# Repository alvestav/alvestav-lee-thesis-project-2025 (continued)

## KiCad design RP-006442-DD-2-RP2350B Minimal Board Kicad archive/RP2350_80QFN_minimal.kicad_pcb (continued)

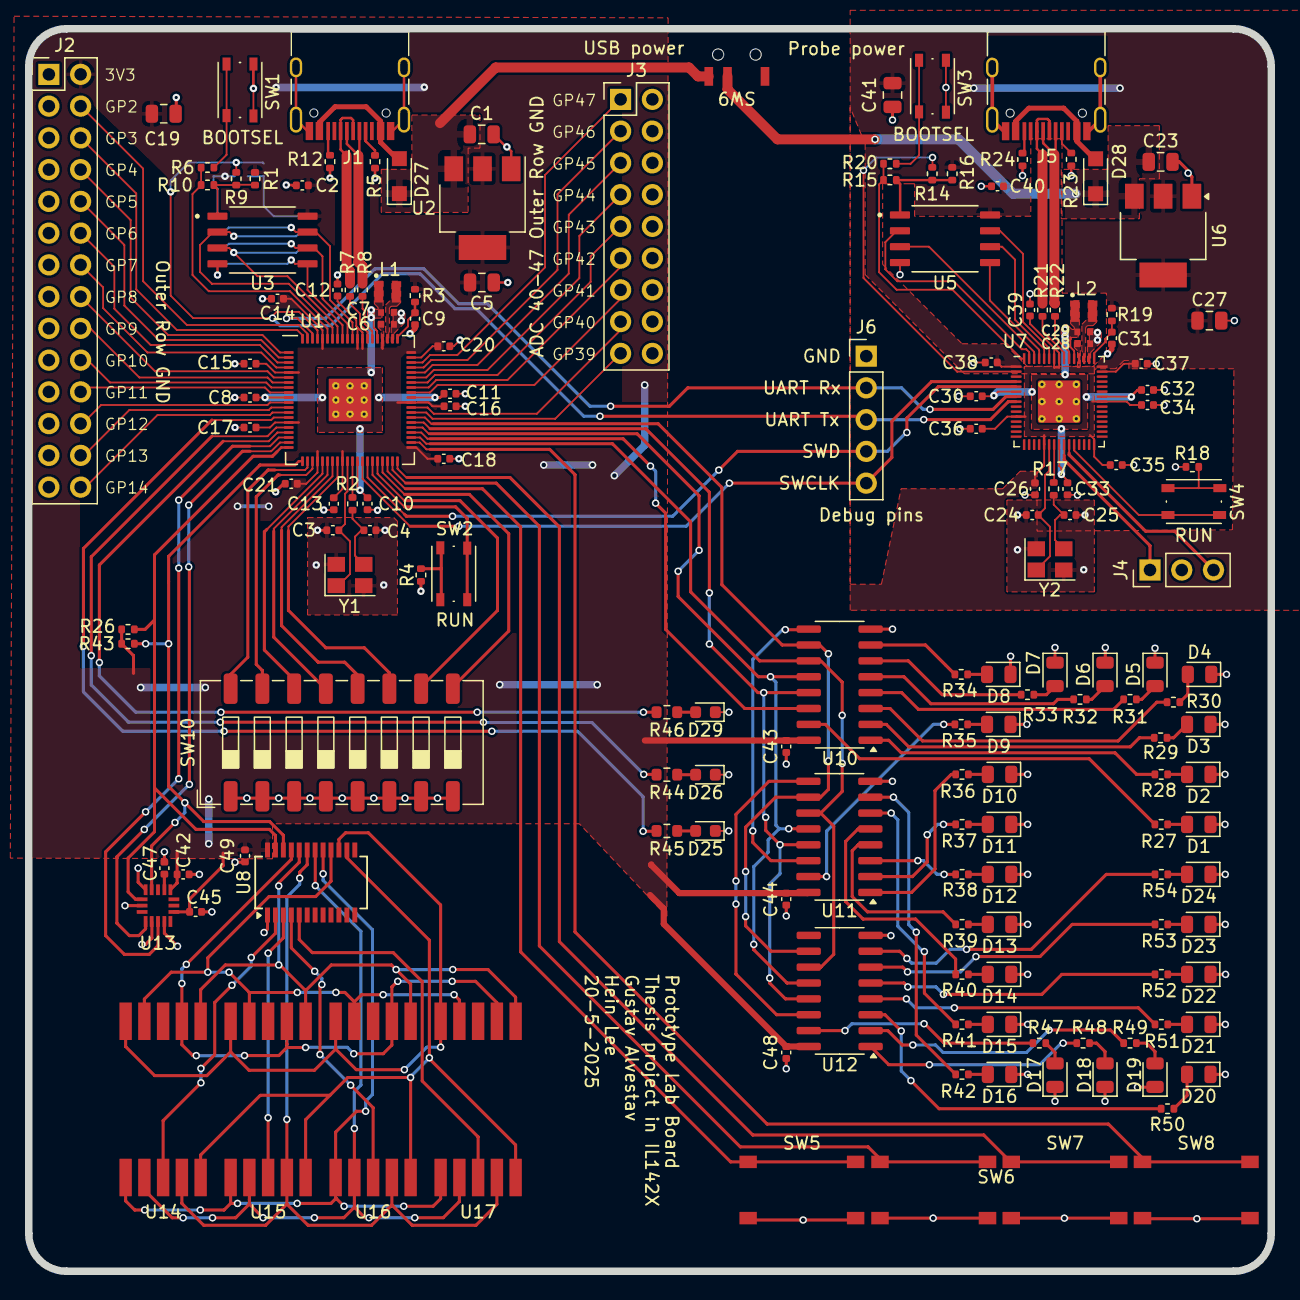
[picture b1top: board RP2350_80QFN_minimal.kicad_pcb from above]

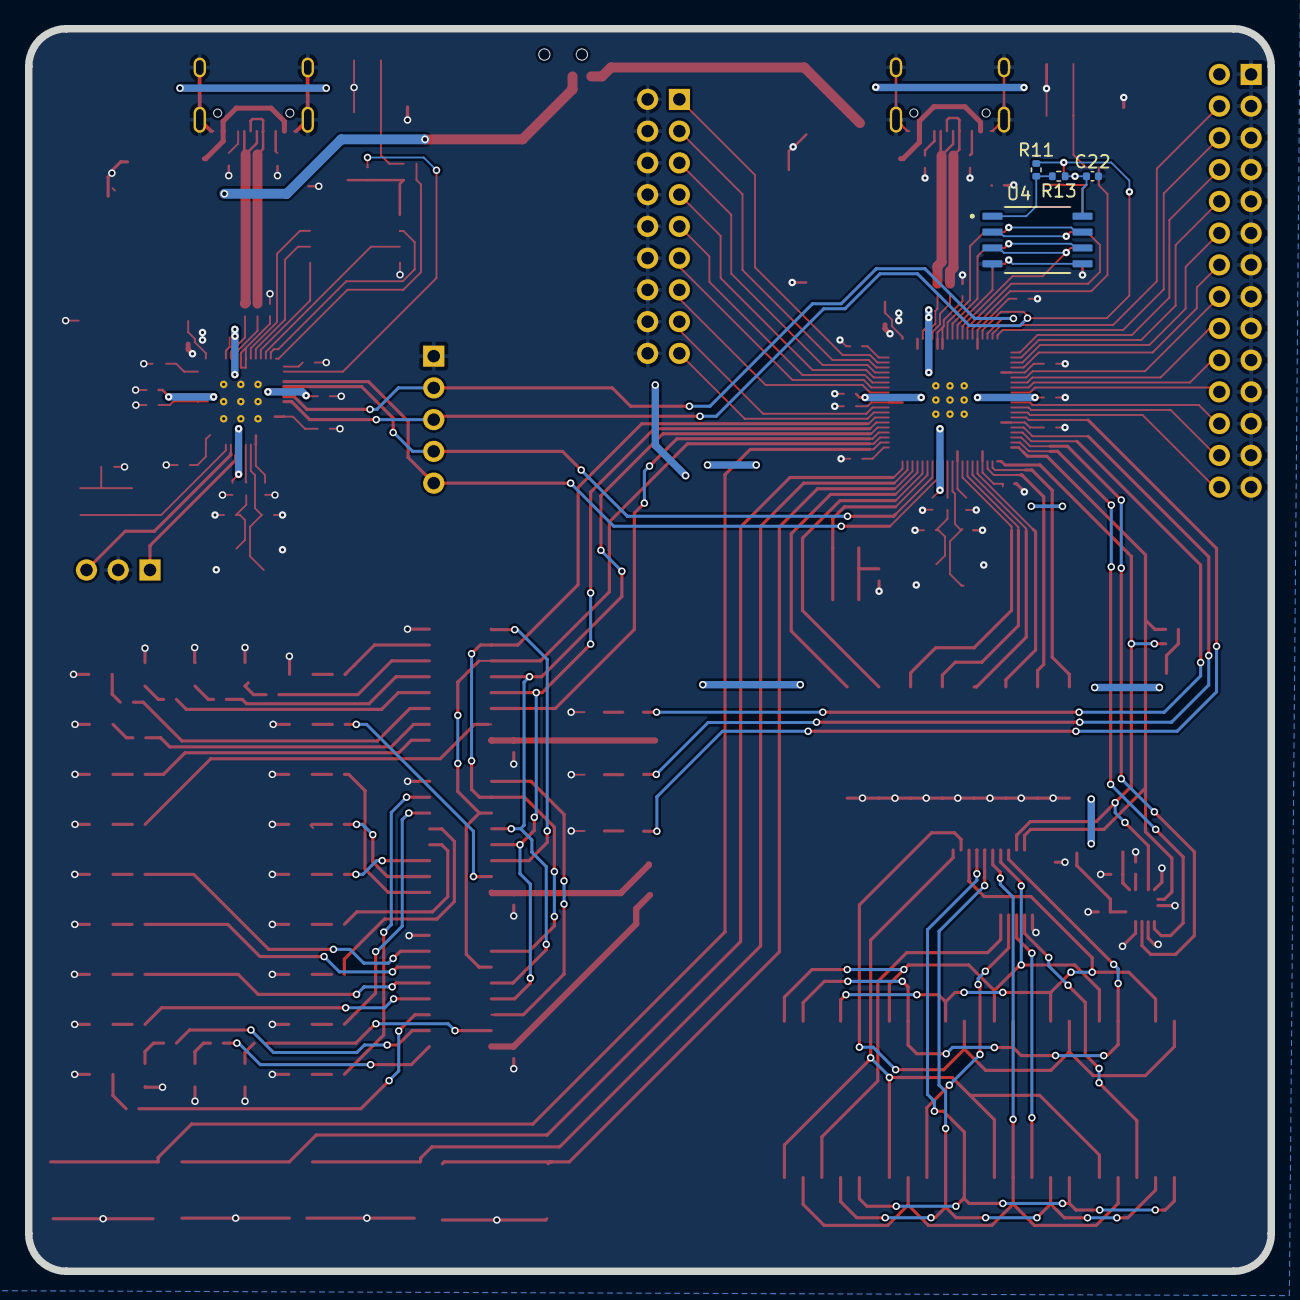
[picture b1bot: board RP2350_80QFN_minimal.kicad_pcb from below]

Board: 2 copper layers, 99.4 x 99.4 mm, 166 parts (4 on the bottom side), 170 nets.

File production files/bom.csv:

Designator,Footprint,Quantity,Value,LCSC Part #
"C1, C19, C23, C27, C41, C5",0805,6,10u,C15850
"C10, C28, C29, C31, C32, C45, C6, C7, C9",0402,9,4.7u,C23733
"C11, C12, C13, C14, C15, C16, C17, C18, C2, C20, C21, C26, C30, C33, C34, C35, C36, C37, C38, C39, C40, C42, C43, C44, C47, C48, C49, C8",0402,28,100n,C1525
"C22, R1, R11, R13, R14, R16, R9",0402,7,DNF,
"C24, C25, C3, C4",0402,4,15p,C1548
"D1, D10, D11, D12, D13, D14, D15, D16, D17, D18, D19, D2, D20, D21, D22, D23, D24, D3, D4, D5, D6, D7, D8, D9",0805,24,LED,C84256
D25,0603,1,EMERALD,C7429914
D26,0603,1,YELLOW,C72038
"D27, D28",Nexperia_CFP3_SOD-123W,2,PMEG6010ELR,C179432
D29,0603,1,RED,C2286
"J1, J5",USB_C_Receptacle_HRO_TYPE-C-31-M-12,2,USB_C_Receptacle_USB2.0_16P,C165948
J2,PinHeader_2x14_P2.54mm_Vertical,1,Conn_02x14_Odd_Even,
J3,PinHeader_2x09_P2.54mm_Vertical,1,Conn_02x09_Odd_Even,
J4,PinHeader_1x03_P2.54mm_Vertical,1,Conn_01x03,
J6,PinHeader_1x05_P2.54mm_Vertical,1,Conn_01x05,
"L1, L2",L_pol_2016,2,3.3u,C42411119
"R10, R15",0402,2,0,C17168
"R12, R23, R24, R5",0402,4,5.1k,C25905
"R17, R18, R2, R20, R4, R6",0402,6,1k,C11702
"R19, R3",0402,2,33,C25105
"R21, R22, R7, R8",0402,4,27,C25100
"R26, R43",0402,2,4.7k,C25900
"R27, R28, R29, R30, R31, R32, R33, R34, R35, R36, R37, R38, R39, R40, R41, R42, R47, R48, R49, R50, R51, R52, R53, R54",0402,24,470,C25117
R44,0603,1,560,C23204
R45,0603,1,180,C22828
R46,0603,1,820,C23253
"SW1, SW2, SW3, SW4",SW_Push_1P1T_NO_Vertical_Wuerth_434133025816,4,SW_Push,C5504987
SW10,SW_DIP_SPSTx08_Slide_9.78x22.5mm_W8.61mm_P2.54mm,1,SW_DIP_x08,C54953
"SW5, SW6, SW7, SW8",SW_Push_K2-1102SP-A4SC-04,4,SW_Push,C83916
SW9,SW_SPDT_G-Switch_MK-12C03-G015,1,SW_SPDT,C2890358
U1,RP2350-QFN-80-1EP_10x10_P0.4mm_EP3.4x3.4mm_ThermalVias,1,RP2350_80QFN,C42415655
"U10, U11, U12",SOIC-16_3.9x9.9mm_P1.27mm,3,74HC595,C5947
U13,QFN50P300X300X100-16N,1,MMA8451QR1,C11360
"U14, U15, U16, U17",GS3011CR-G,4,GS3011CR-G,C22462656
"U2, U6",SOT-223-3_TabPin2,2,NCP1117-3.3_SOT223,C26537
"U3, U5",SOIC127P790X216-8N,2,W25Q128JVS,C97521
U4,SOIC127P790X216-8N,1,DNF,
U7,RP2350-QFN-60-1EP_7x7_P0.4mm_EP3.4x3.4mm_ThermalVias,1,RP2350_60QFN,C42411118
U8,SSOP-24_3.9x8.7mm_P0.635mm,1,HT16K33A-24SSOP,C5444736
"Y1, Y2",Crystal_SMD_3225-4Pin_3.2x2.5mm,2,ABM8-272-T3,C20625731

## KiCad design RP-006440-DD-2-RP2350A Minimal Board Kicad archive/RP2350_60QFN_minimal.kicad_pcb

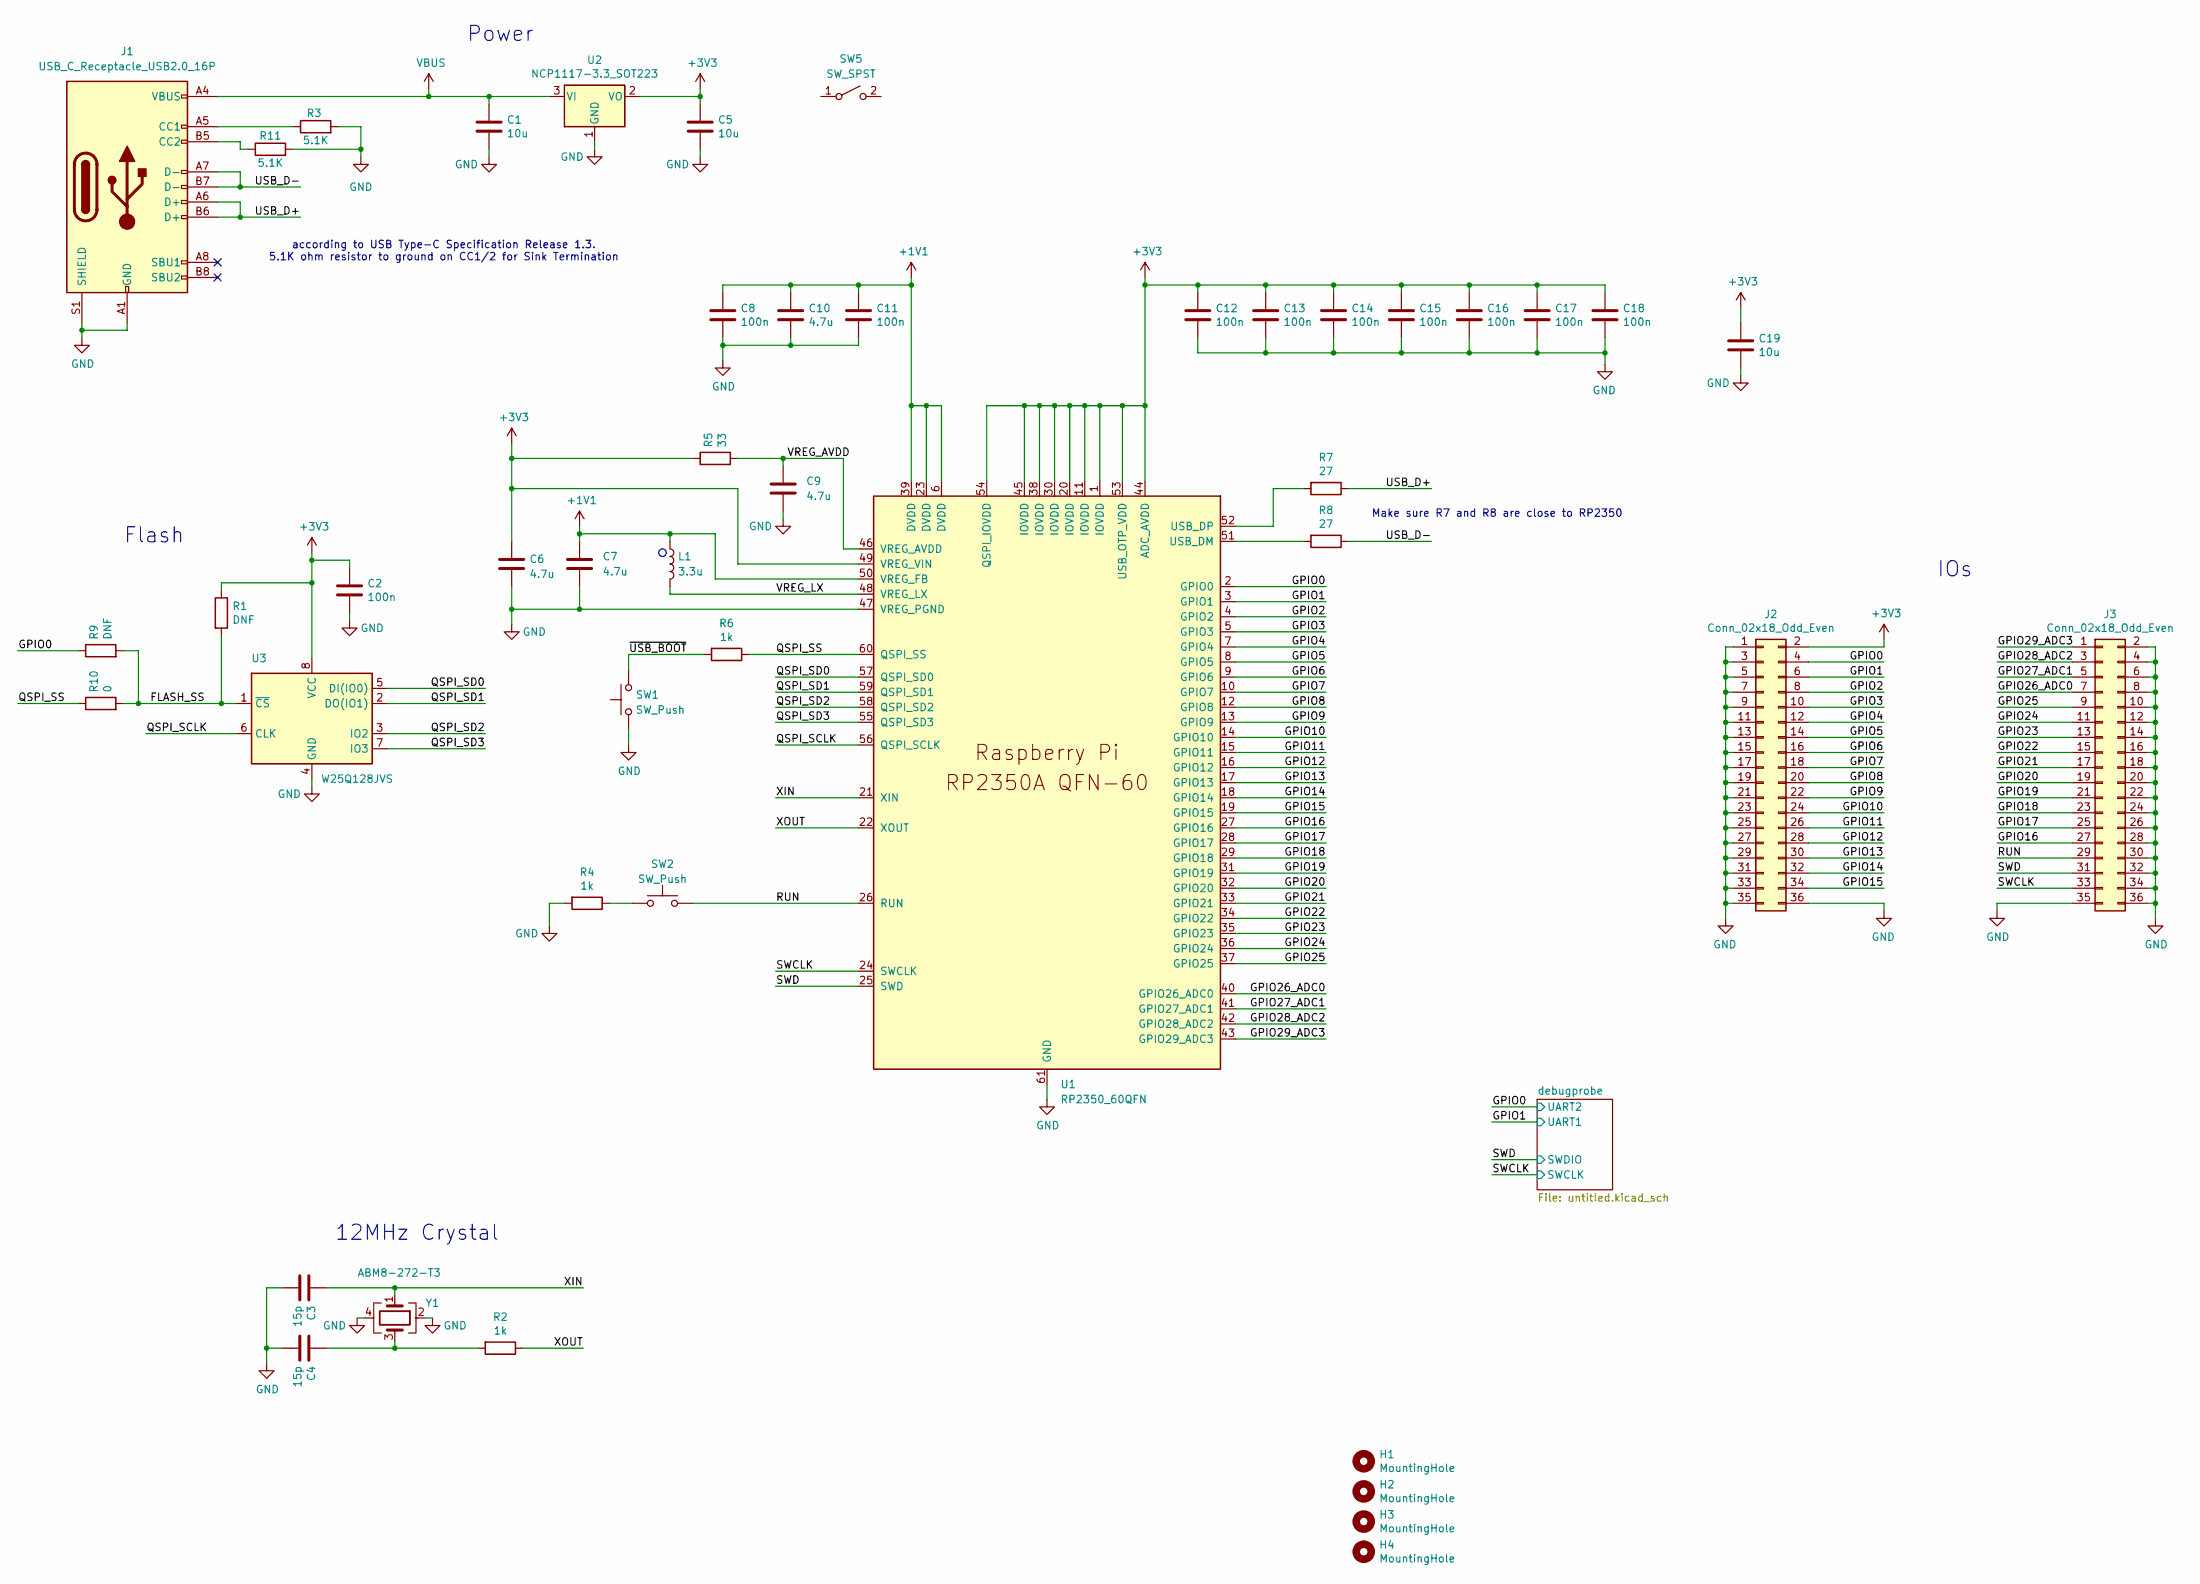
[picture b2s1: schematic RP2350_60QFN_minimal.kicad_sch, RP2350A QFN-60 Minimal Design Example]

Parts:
C1, C5, C19: 10u; C_0805_2012Metric
C2, C8, C11, C12, C13, C14, C15, C16, C17, C18: 100n; C_0402_1005Metric
C3, C4: 15p; C_0402_1005Metric
C6, C7: 4.7u; C_0402_1005Metric_small_pads
C9, C10: 4.7u; C_0402_1005Metric
H1, H2, H3, H4: MountingHole; MountingHole_2.7mm_M2.5
J1: USB_C_Receptacle_USB2.0_16P; USB_C_Receptacle_HRO_TYPE-C-31-M-12
J2, J3: Conn_02x18_Odd_Even; PinHeader_2x18_P2.54mm_Vertical
L1: 3.3u; L_pol_2016
R1, R9: DNF; R_0402_1005Metric
R2, R4, R6: 1k; R_0402_1005Metric
R3, R11: 5.1K; R_0402_1005Metric
R5: 33; R_0402_1005Metric
R7, R8: 27; R_0402_1005Metric
R10: 0; R_0402_1005Metric
SW1, SW2: SW_Push; SW_Push_1P1T_NO_Vertical_Wuerth_434133025816
SW5: SW_SPST; SW_DPDT_CK_JS202011JCQN
U1: RP2350_60QFN; RP2350-QFN-60-1EP_7x7_P0.4mm_EP3.4x3.4mm_ThermalVias
U2: NCP1117-3.3_SOT223; SOT-223-3_TabPin2
U3: W25Q128JVS; SOIC-8_5.23x5.23mm_P1.27mm
Y1: ABM8-272-T3; Crystal_SMD_3225-4Pin_3.2x2.5mm

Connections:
+1V1: C7.1, C8.1, C10.1, C11.1, L1.1, U1.6 (DVDD), U1.23 (DVDD), U1.39 (DVDD), U1.50 (VREG_FB); also elsewhere on the board
+3V3: C2.1, C5.1, C6.1, C12.1, C13.1, C14.1, C15.1, C16.1, C17.1, C18.1, C19.1, J2.2, R1.1, R5.1, U1.1 (IOVDD), U1.11 (IOVDD), U1.20 (IOVDD), U1.30 (IOVDD), U1.38 (IOVDD), U1.44 (ADC_AVDD), U1.45 (IOVDD), U1.49 (VREG_VIN), U1.53 (USB_OTP_VDD), U1.54 (QSPI_IOVDD), U2.2 (VO), U3.8 (VCC); also elsewhere on the board
/FLASH_SS: R1.2, R9.2, R10.2, U3.1 (~CS)
/GPIO0: J2.4, R9.1, U1.2 (GPIO0); also elsewhere on the board
/GPIO1: J2.6, U1.3 (GPIO1); also elsewhere on the board
/GPIO2: J2.8, U1.4 (GPIO2)
/GPIO3: J2.10, U1.5 (GPIO3)
/GPIO4: J2.12, U1.7 (GPIO4)
/GPIO5: J2.14, U1.8 (GPIO5)
/GPIO6: J2.16, U1.9 (GPIO6)
/GPIO7: J2.18, U1.10 (GPIO7)
/GPIO8: J2.20, U1.12 (GPIO8)
/GPIO9: J2.22, U1.13 (GPIO9)
/GPIO10: J2.24, U1.14 (GPIO10)
/GPIO11: J2.26, U1.15 (GPIO11)
/GPIO12: J2.28, U1.16 (GPIO12)
/GPIO13: J2.30, U1.17 (GPIO13)
/GPIO14: J2.32, U1.18 (GPIO14)
/GPIO15: J2.34, U1.19 (GPIO15)
/GPIO16: J3.27, U1.27 (GPIO16)
/GPIO17: J3.25, U1.28 (GPIO17)
/GPIO18: J3.23, U1.29 (GPIO18)
/GPIO19: J3.21, U1.31 (GPIO19)
/GPIO20: J3.19, U1.32 (GPIO20)
/GPIO21: J3.17, U1.33 (GPIO21)
/GPIO22: J3.15, U1.34 (GPIO22)
/GPIO23: J3.13, U1.35 (GPIO23)
/GPIO24: J3.11, U1.36 (GPIO24)
/GPIO25: J3.9, U1.37 (GPIO25)
/GPIO26_ADC0: J3.7, U1.40 (GPIO26_ADC0)
/GPIO27_ADC1: J3.5, U1.41 (GPIO27_ADC1)
/GPIO28_ADC2: J3.3, U1.42 (GPIO28_ADC2)
/GPIO29_ADC3: J3.1, U1.43 (GPIO29_ADC3)
/QSPI_SCLK: U1.56 (QSPI_SCLK), U3.6 (CLK)
/QSPI_SD0: U1.57 (QSPI_SD0), U3.5 (DI(IO0))
/QSPI_SD1: U1.59 (QSPI_SD1), U3.2 (DO(IO1))
/QSPI_SD2: U1.58 (QSPI_SD2), U3.3 (IO2)
/QSPI_SD3: U1.55 (QSPI_SD3), U3.7 (IO3)
/QSPI_SS: R6.1, R10.1, U1.60 (QSPI_SS)
/RUN: J3.29, SW2.2, U1.26 (RUN)
/SWCLK: J3.33, U1.24 (SWCLK); also elsewhere on the board
/SWD: J3.31, U1.25 (SWD); also elsewhere on the board
/USB_D+: J1.A6 (D+), J1.B6 (D+), R7.1
/USB_D-: J1.A7 (D-), J1.B7 (D-), R8.1
/VREG_AVDD: C9.1, R5.2, U1.46 (VREG_AVDD)
/VREG_LX: L1.2, U1.48 (VREG_LX)
/XIN: C3.1, U1.21 (XIN), Y1.1
/XOUT: R2.1, U1.22 (XOUT)
/~USB_BOOT: R6.2, SW1.2
GND: C1.2, C2.2, C3.2, C4.2, C5.2, C6.2, C7.2, C8.2, C9.2, C10.2, C11.2, C12.2, C13.2, C14.2, C15.2, C16.2, C17.2, C18.2, C19.2, J1.A1 (GND), J1.A12 (GND), J1.B1 (GND), J1.B12 (GND), J1.S1 (SHIELD), J2.1, J2.3, J2.5, J2.7, J2.9, J2.11, J2.13, J2.15, J2.17, J2.19, J2.21, J2.23, J2.25, J2.27, J2.29, J2.31, J2.33, J2.35, J2.36, J3.2, J3.4, J3.6, J3.8, J3.10, J3.12, J3.14, J3.16, J3.18, J3.20, J3.22, J3.24, J3.26, J3.28, J3.30, J3.32, J3.34, J3.35, J3.36, R3.2, R4.2, R11.2, SW1.1, U1.47 (VREG_PGND), U1.61 (GND), U2.1 (GND), U3.4 (GND), Y1.2, Y1.4; also elsewhere on the board
unnamed: C4.1, R2.2, Y1.3
unnamed: J1.A5 (CC1), R3.1
unnamed: J1.B5 (CC2), R11.1
unnamed: R4.1, SW2.1
unnamed: R8.2, U1.51 (USB_DM)
unnamed: R7.2, U1.52 (USB_DP)
VBUS: C1.1, J1.A4 (VBUS), J1.A9 (VBUS), J1.B4 (VBUS), J1.B9 (VBUS), U2.3 (VI); also elsewhere on the board

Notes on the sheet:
according to USB Type-C Specification Release 1.3. 5.1K ohm resistor to ground on CC1/2 for Sink Termination
IOs
Flash
Make sure R7 and R8 are close to RP2350
12MHz Crystal
Power

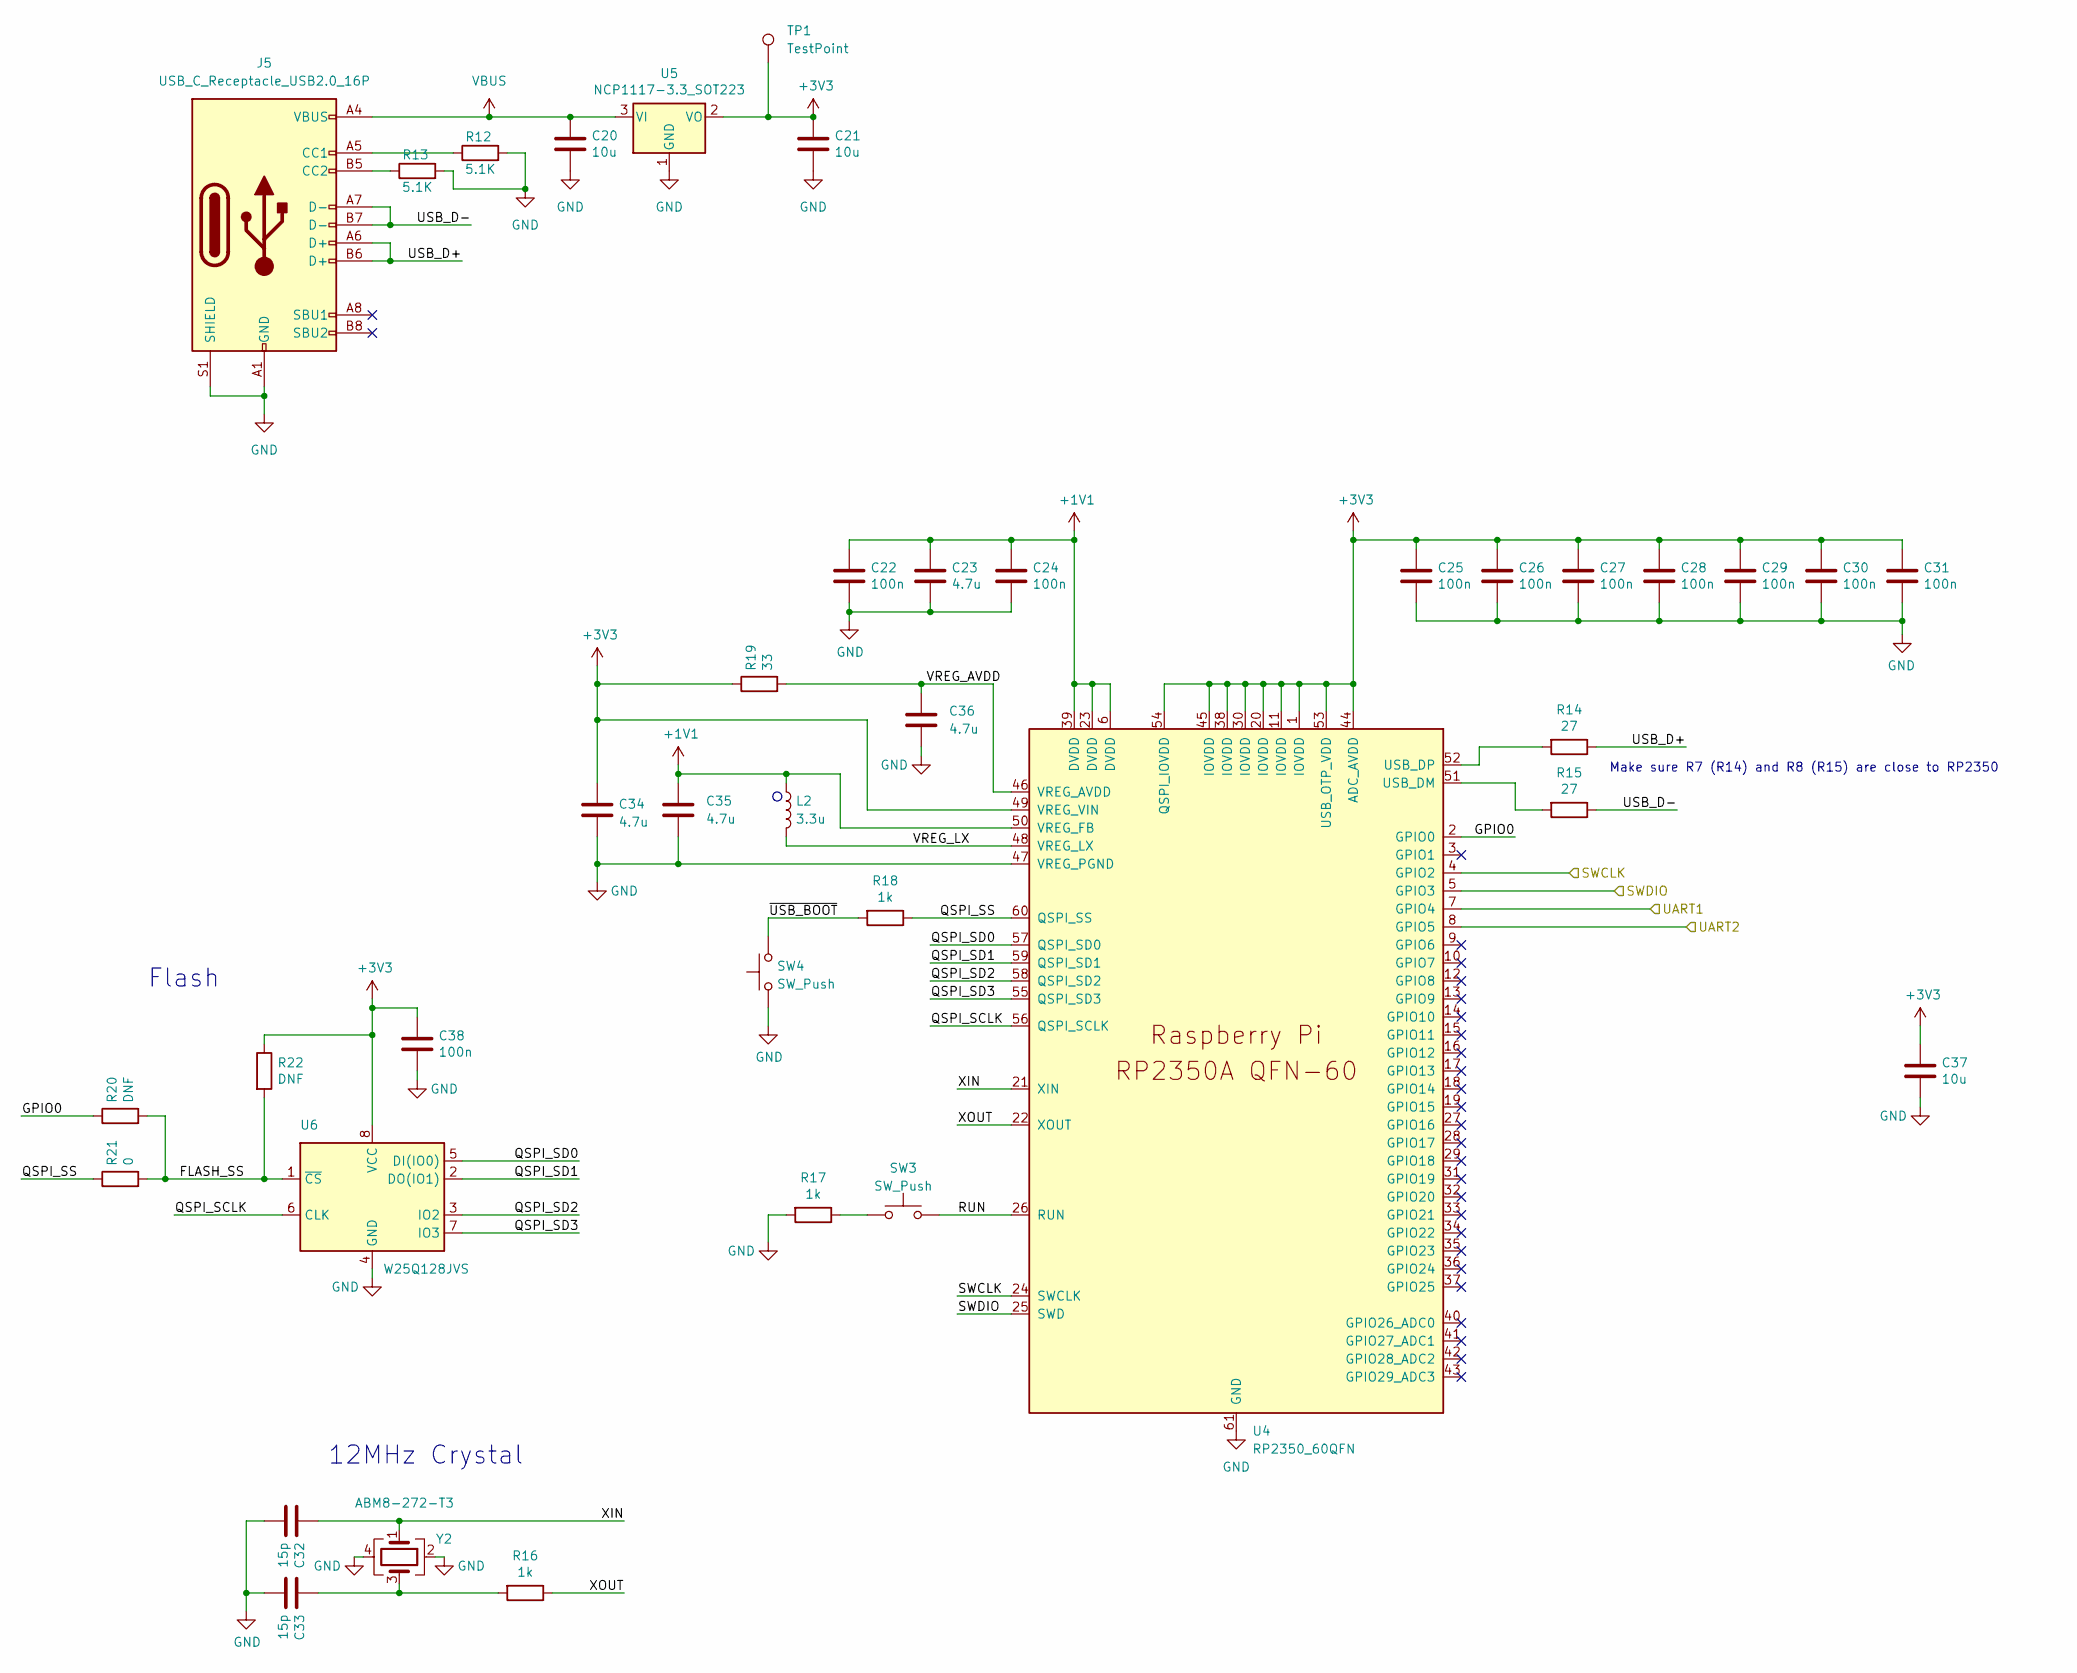
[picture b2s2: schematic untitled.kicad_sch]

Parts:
C20, C21, C37: 10u; C_0805_2012Metric
C22, C24, C25, C26, C27, C28, C29, C30, C31, C38: 100n; C_0402_1005Metric
C23, C36: 4.7u; C_0402_1005Metric
C32, C33: 15p; C_0402_1005Metric
C34, C35: 4.7u; C_0402_1005Metric_small_pads
J5: USB_C_Receptacle_USB2.0_16P; USB_C_Receptacle_HRO_TYPE-C-31-M-12
L2: 3.3u; L_pol_2016
R12, R13: 5.1K; R_0402_1005Metric
R14, R15: 27; R_0402_1005Metric
R16, R17, R18: 1k; R_0402_1005Metric
R19: 33; R_0402_1005Metric
R20, R22: DNF; R_0402_1005Metric
R21: 0; R_0402_1005Metric
SW3, SW4: SW_Push; SW_Push_1P1T_NO_Vertical_Wuerth_434133025816
TP1: TestPoint; TestPoint_Pad_1.5x1.5mm
U4: RP2350_60QFN; RP2350-QFN-60-1EP_7x7_P0.4mm_EP3.4x3.4mm_ThermalVias
U5: NCP1117-3.3_SOT223; SOT-223-3_TabPin2
U6: W25Q128JVS; SOIC-8_5.23x5.23mm_P1.27mm
Y2: ABM8-272-T3; Crystal_SMD_3225-4Pin_3.2x2.5mm

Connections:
+1V1: C22.1, C23.1, C24.1, C35.1, L2.1, U4.6 (DVDD), U4.23 (DVDD), U4.39 (DVDD), U4.50 (VREG_FB); also elsewhere on the board
+3V3: C21.1, C25.1, C26.1, C27.1, C28.1, C29.1, C30.1, C31.1, C34.1, C37.1, C38.1, R19.1, R22.1, TP1.1, U4.1 (IOVDD), U4.11 (IOVDD), U4.20 (IOVDD), U4.30 (IOVDD), U4.38 (IOVDD), U4.44 (ADC_AVDD), U4.45 (IOVDD), U4.49 (VREG_VIN), U4.53 (USB_OTP_VDD), U4.54 (QSPI_IOVDD), U5.2 (VO), U6.8 (VCC); also elsewhere on the board
/GPIO0: U4.8 (GPIO5); also elsewhere on the board
/GPIO1: U4.7 (GPIO4); also elsewhere on the board
/SWCLK: U4.4 (GPIO2), U4.24 (SWCLK); also elsewhere on the board
/SWD: U4.5 (GPIO3), U4.25 (SWD); also elsewhere on the board
/debugprobe/FLASH_SS: R20.2, R21.2, R22.2, U6.1 (~CS)
/debugprobe/GPIO0: R20.1, U4.2 (GPIO0)
/debugprobe/QSPI_SCLK: U4.56 (QSPI_SCLK), U6.6 (CLK)
/debugprobe/QSPI_SD0: U4.57 (QSPI_SD0), U6.5 (DI(IO0))
/debugprobe/QSPI_SD1: U4.59 (QSPI_SD1), U6.2 (DO(IO1))
/debugprobe/QSPI_SD2: U4.58 (QSPI_SD2), U6.3 (IO2)
/debugprobe/QSPI_SD3: U4.55 (QSPI_SD3), U6.7 (IO3)
/debugprobe/QSPI_SS: R18.1, R21.1, U4.60 (QSPI_SS)
/debugprobe/RUN: SW3.2, U4.26 (RUN)
/debugprobe/USB_D+: J5.A6 (D+), J5.B6 (D+), R14.1
/debugprobe/USB_D-: J5.A7 (D-), J5.B7 (D-), R15.1
/debugprobe/VREG_AVDD: C36.1, R19.2, U4.46 (VREG_AVDD)
/debugprobe/VREG_LX: L2.2, U4.48 (VREG_LX)
/debugprobe/XIN: C32.1, U4.21 (XIN), Y2.1
/debugprobe/XOUT: R16.1, U4.22 (XOUT)
/debugprobe/~USB_BOOT: R18.2, SW4.2
GND: C20.2, C21.2, C22.2, C23.2, C24.2, C25.2, C26.2, C27.2, C28.2, C29.2, C30.2, C31.2, C32.2, C33.2, C34.2, C35.2, C36.2, C37.2, C38.2, J5.A1 (GND), J5.A12 (GND), J5.B1 (GND), J5.B12 (GND), J5.S1 (SHIELD), R12.2, R13.2, R17.2, SW4.1, U4.47 (VREG_PGND), U4.61 (GND), U5.1 (GND), U6.4 (GND), Y2.2, Y2.4; also elsewhere on the board
unnamed: C33.1, R16.2, Y2.3
unnamed: J5.A5 (CC1), R12.1
unnamed: J5.B5 (CC2), R13.1
unnamed: R17.1, SW3.1
unnamed: R15.2, U4.51 (USB_DM)
unnamed: R14.2, U4.52 (USB_DP)
VBUS: C20.1, J5.A4 (VBUS), J5.A9 (VBUS), J5.B4 (VBUS), J5.B9 (VBUS), U5.3 (VI); also elsewhere on the board

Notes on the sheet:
12MHz Crystal
Flash
Make sure R7 (R14) and R8 (R15) are close to RP2350

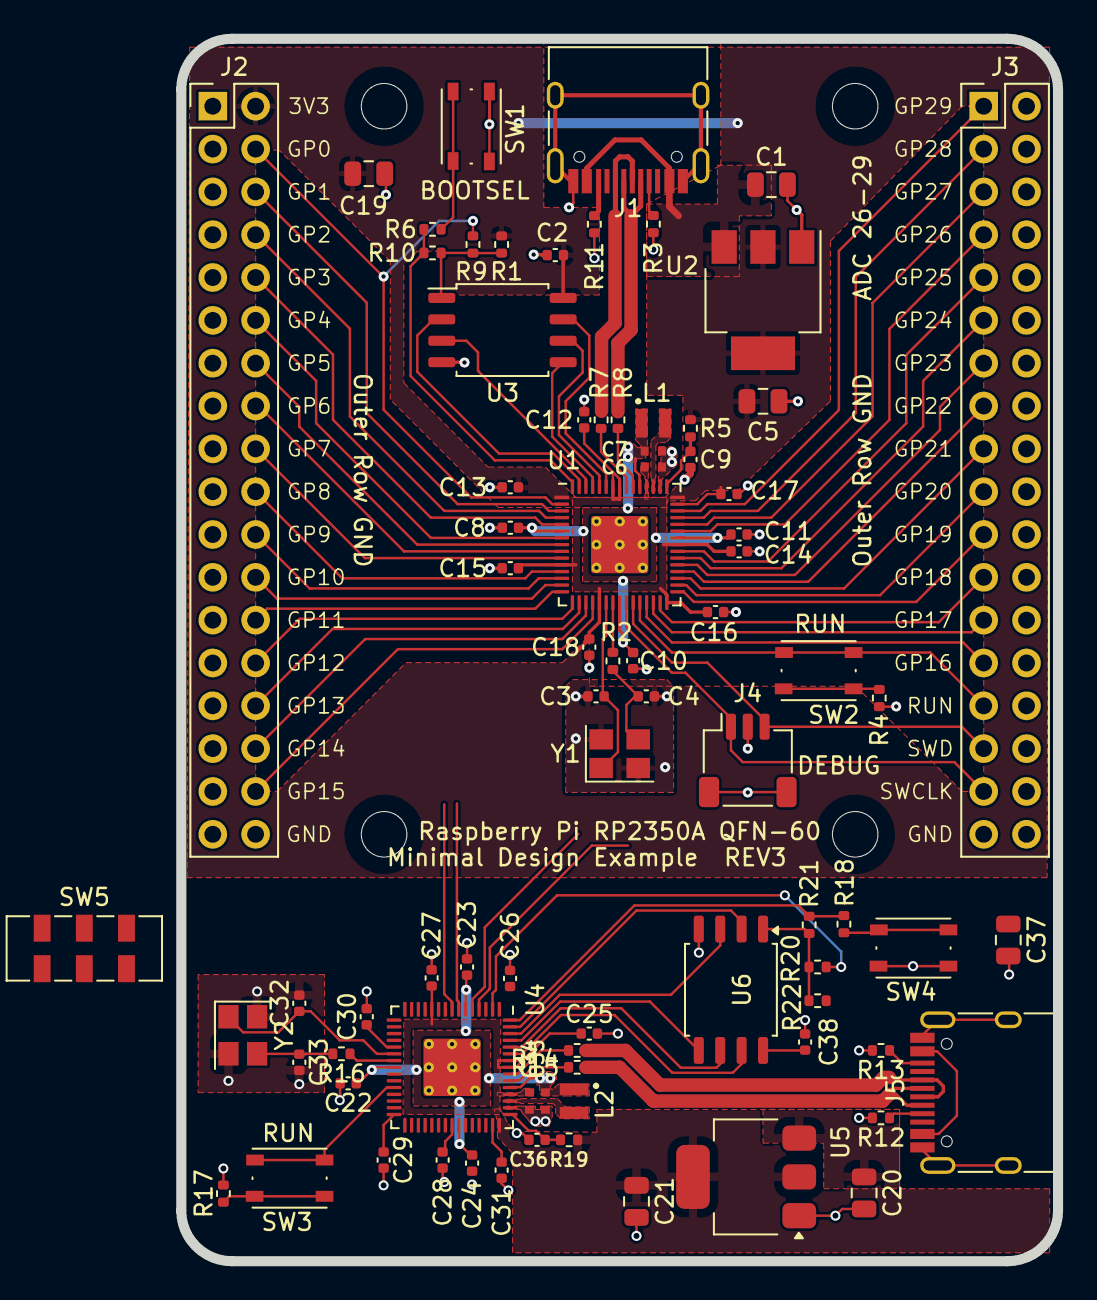
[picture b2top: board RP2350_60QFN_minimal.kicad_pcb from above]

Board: 2 copper layers, 52.0 x 72.5 mm, 85 parts (1 on the bottom side), 79 nets.

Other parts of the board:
J4: SM03B-SRSS-TB; JST_SH_SM03B-SRSS-TB_1x03-1MP_P1.00mm_Horizontal

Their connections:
/SWCLK: J4.1; also elsewhere on the board
/SWD: J4.3; also elsewhere on the board
GND: J4.2, J4.MP (MountPin); also elsewhere on the board

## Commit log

2025-03-21 test commit
2025-03-21 Removed schematic symbol
    removed micro usb symbol from schematic
2025-03-24 Added schematic page, symbol library
    added schematic page and RP2040 symbol library from RP2040 minimal pcb project.
2025-03-24 added usb-c to pcb editor
2025-03-24 added 5.1k ohm resistors to usb-c CC1 and CC2
2025-03-25 moved usb type-c on pcb
    removed micro usb footprint
2025-03-31 change edgecuts dimensions
    change to edgecuts in pcb and changes to schematic
2025-03-31 change pcb edgecuts and add comments
2025-04-09 Replaced project with RP2350A variant
    Replaced the RP2350B reference project files with RP2350A reference files
2025-04-09 USB-C schematic
    replaced micro usb schematic with usb 2.0 type c plus 5.1k resistors on CC1/2
2025-04-09 Update PCB
    added usbc receptacle and resistor footprints to pcb
2025-04-09 Schematic text
2025-04-10 .lck to gitignore
2025-04-10 Added debugprobe schematic
    Added debugprobe schematic and started working on debug probe circuit
2025-04-11 small change
2025-04-15 Added footprints to PCB
    debugger footprints pcb
2025-04-16 Update .gitignore
    added kicad #auto_saved_files# to gitignore
2025-04-16 Added secondary memory to schematic
2025-04-22 Updated PCB
2025-04-22 Update schematic and PCB
    Added hierarchal labels between main and debugprobe, connected the pins.
2025-04-24 Added minimal RP2350B reference project
2025-04-24 first save
2025-04-24 Imported RP2350A symbol
2025-04-24 Imported RP2350A footprint and symbols
2025-04-24 Added circuit schematic for debugprobe
2025-04-24 Added hex displays schematic sheet
2025-04-25 added schematic page
2025-04-25 added led symbol
2025-04-25 Created a sheet for LEDs
2025-04-25 added hierarchical label to root
2025-04-25 added leds schematic page
2025-04-25 Placed hierarchical labels in debugprobe
2025-04-25 Added debugger labels to root
    moved some symbols around
2025-04-28 Assigned footprints to symbols
2025-04-28 Added debugprobe components to pcb
    added pinheader connector to debug probe
2025-04-28 Created HT16K33-28SOP symbol
    assigned new symbol footprint the pre-defined footprint for SOP-28 package
2025-04-29 Update hex displays
    Added 7-segment display symbol, labels, i2c pull-up resistors, capacitor.
    Synced added components to pcb.
2025-04-29 Update to pcb
2025-04-29 Update to PCB
    Added debug UART trace to main microcontroller
2025-05-01 LED Sheet , Two Buttons
    Attempt at completing LED sheet with resistors and GPIO connections.
    Also two buttons in the Button sheet.
2025-05-02 Update RP2350_80QFN_minimal.kicad_pcb
    Changed edge cut dimensions to 10mmX10mm
2025-05-02 Small update to pcb
2025-05-02 Update leds.kicad_sch
    added 74hc595 soic symbol
2025-05-02 leds
2025-05-02 Update RP2350_80QFN_minimal.kicad_pcb
    Added vbus trace to lower board
2025-05-02 Update RP2350_80QFN_minimal.kicad_pcb
    changed debugger uart trace to 0.25 mm
2025-05-02 Updated leds schematic
    Added 74HC595, leds and resistors
2025-05-02 Connected GPIOs to Shift Register pins
2025-05-02 Update RP2350_80QFN_minimal.kicad_sch
    added some description text
2025-05-02 Update leds.kicad_sch
    Added description text
2025-05-02 Update hexdisplays.kicad_sch
    added NCP1117-5.0 linear voltage regulator symbol
2025-05-02 Update hexdisplays.kicad_sch
    Created symbol for a HT16K33A-24SSOP ic with existing SSOP-24 footprint
2025-05-04 Swith buttons added 22*11mm
    Button_Switch_SMD:SW_DIP_SPSTx08_Slide_Omron_A6S-810x_W8.9mm_P2.54mm
2025-05-05 Update to schematic and pcb
    Changed ht16k33 package from 28SOP to 24SSOP
    Placed pcb footprints
2025-05-05 text
2025-05-05 Update RP2350_80QFN_minimal.kicad_pcb
    Connected led and shift register wires
2025-05-05 wires to hex display
2025-05-05 Update RP2350_80QFN_minimal.kicad_pcb
    Connected wires to switch and buttons
2025-05-06 VBUS to VDD connection
2025-05-06 Update
    fixed some errors in electrical rules checker
2025-05-06 small update
2025-05-06 Remove mounting holes
2025-05-06 Update RP2350_80QFN_minimal.kicad_pcb
    added silkscreen text
2025-05-07 Increase width of some traces
2025-05-08 Update RP2350_80QFN_minimal.kicad_pcb
    Small copper fill fix
2025-05-09 Update RP2350_80QFN_minimal.kicad_pcb
    moved hex display outside of 5mm of pcb edge
2025-05-09 Update RP2350_80QFN_minimal.kicad_pcb
    Fixed some DRC errors
2025-05-12 Update pushbutton footprints on pcb
    Changed from omron pushbutton footprints to custom footprints for JLCPCB part
2025-05-13 Update schematic
    added schottky diode to vbus on microcontroller and debug probe
2025-05-13 Update to schematic and pcb
    Changed:
    - Added 100n decoupling capacitors to both 74HC595
    - Changed ground plane to single common ground plane
    - Added schottky diode to usb vbus inputs, creating separate vbus and vsys
2025-05-13 Added LIS2DW12TR component
    - added LIS2DW12TR symbol and footprint
    - added circuit schematic for LIS2DW12TR
2025-05-13 Update accelerometer
    Added accelerometer circuit to PCB editor
2025-05-14 Red, Yellow, Emerald plus resistors, to GPIOs
2025-05-14 Update PCB
    Created footprint for SW_SPDT symbol
    Added switch footprint to PCB and connected VSYS
2025-05-14 Changed Resistor numbers
2025-05-14 8 more LEDs + 3rd Shift register
2025-05-14 udpate
2025-05-14 Big update
2025-05-15 Fabrication toolkit production
    Created production folder from fabrication toolkit
2025-05-15 Added capacitor to LED driver power input
2025-05-15 Changed edgecuts to within 100mmX100mm
2025-05-15 Datasheet och länk till JLCPCP för resistorna
2025-05-15 gerber files update
2025-05-15 Update 8-bit switch, footprint, datasheet
2025-05-16 Measurements
2025-05-16 PNG and LCSC numbers
2025-05-16 removed production and gerbers
2025-05-16 Revert "Merge branch 'main' of https://github.com/alvestav/alvestav-lee-thesis-project-2025"
    This reverts commit 492c910224f218c530b72a86f026f374fdb1ba99, reversing
    changes made to 8b8c3067a07da89d4cec6960bc27222e60866367.
2025-05-16 Update gitignore
2025-05-16 Added LCSC numbers to parts
2025-05-16 Added Emerald LED LCSC number
2025-05-16 Fixed overlapping silkscreen
2025-05-16 Updated PCB LSCS values
2025-05-16 New Flash memory footprint
    footprint from snapmagic
2025-05-16 Added MMA8451QR1 symbol and footprint
    MMA8451QR1 Accelerometer
2025-05-16 New accelerometer schematic
    MMA8451QR1
2025-05-16 Accelerometer footprint added
2025-05-18 Added GS3011CR-G symbol and footprint
    GS3011CR-G SMD 7-segment display from jlcpcb
2025-05-18 Testing electrical rules
2025-05-19 Update pcb
2025-05-19 Update GS3011CR-G footprint
2025-05-19 Update GS3011CR-G.kicad_mod
    added link to datasheed
2025-05-19 Added Accelerometer datasheet and link to JLCPCB
2025-05-19 Update hex display pcb traces
2025-05-20 Update usb power switch
2025-05-20 Update RP2350_80QFN_minimal.kicad_pcb
    moved switch 1 mm
2025-05-20 Update accelerometer
    Pulled SA0 pin to ground for slave address 0011100 (0x1C)
2025-05-20 Added LCSC number to accelerometer
2025-05-20 Production files
2025-05-20 Update production files
2025-05-20 Update csv files in gitignore and bom and positions cvs files
2025-05-21 Created file for switch footprint
2025-05-21 Comment text
2025-05-22 Exported Schematics as SVG
2025-05-22 Created Figures
2025-06-02 Added test program
    Added test program based on ht16k33_i2c pico example
2025-08-15 Updated accelerometer sensitivity numbers
    Fixed g-force reading
2025-08-15 Update ht16k33_i2c.c
    changed program to detect a difference in button status to trigger traffic light leds instead of directly lighting leds based on status of buttons
